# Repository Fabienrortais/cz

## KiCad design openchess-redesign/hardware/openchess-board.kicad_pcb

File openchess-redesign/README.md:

# OpenChess PCB redesign

A complete, single-PCB redesign of the OpenChess smart chess board
(https://joojoooo.github.io/OpenChess/) that keeps **100 % firmware
compatibility** with upstream (including the pre-built binaries), while
replacing the hand-wired "plastic PCB" + perfboard with one assembled board.

## What is on the board

- 8 x 8 squares, **40 mm pitch** (parametric), board 340 x 374 mm, 2 layers.
- Per square: one SOT-23 Hall switch at the square centre (under a 12 mm iron
  disc, silkscreen circle marks it), one WS2812B 5050 LED 9 mm below the
  centre, one 100 nF decoupling cap.
- Column drive: 74HCT595 -> 8 x 1k -> 8 x S8550 PNP high-side switches, one
  under each file, feeding switched +5V up a dedicated trace (same scheme as
  upstream, `SR_INVERT_OUTPUTS = PNP`).
- Rows: sensor open-collector outputs wired-OR per rank, 10k pull-up to 3.3 V,
  straight to the ESP32 GPIOs used by the upstream defaults.
- Controller strip (bottom 42 mm): ESP32-WROOM-32E, CH340C USB-UART with the
  DevKitC auto-reset circuit, RESET/BOOT buttons, AMS1117-3.3, USB-C
  (5 V/3 A, 5.1k CC pull-downs, 3 A polyfuse), optional JST-XH 5 V/4 A input,
  2 x 470 uF bulk, 74AHCT1G125 level shifter for the LED data.
- Power distribution: a 4 mm +5V bus along the strip (B.Cu) and a 2 mm vertical
  +5V bus per file; GND pours on both layers stitched with vias at every square
  corner.
- GPIO map = upstream defaults, so the firmware needs no changes:
  LED IO32, SR SER IO33, SRCLK IO14, RCLK IO26, rows IO4,16,17,18,19,21,22,23.

## Optional battery (both variants)

An IP5306 power-bank IC (Injoinic, LCSC C181692) charges a single Li-ion /
LiPo cell from the USB-C input (2.1 A) and boosts it to 5 V (2.4 A max) for
the board. It is selected with the 3-pin jumper **JP1**:

| JP1 | Bus fed from | Use |
|---|---|---|
| 1-2 | fuse output (USB-C or J2 directly) | no battery fitted; U6/L1/C77-C79/J5/SW3 can be left unpopulated |
| 2-3 | IP5306 VOUT (battery boost, pass-through while charging) | battery fitted on J5 (JST-PH 2.0 mm, + on pin 1) |

Without a battery: use the `-nobattery` BOM/CPL files (block unpopulated),
jumper JP1 1-2, and power through USB-C or J2 as on a board without the block.
SW3 is the IP5306 key (short press on, long press off, it also turns off by
itself below about 45 mA, which the ESP32 never reaches). Power budget: the
boost delivers 2.4 A, so with the battery keep the LED brightness moderate
(all 64 LEDs full white need 3.8 A); a 3000 mAh cell runs the board for
roughly 6-8 h of normal play. Set `OPENCHESS_BATTERY=0` before building to
remove the block entirely.

## Two variants

| Variant | Controller | Output folders | Use when |
|---|---|---|---|
| `module` (default) | ESP32-WROOM-32E soldered on the board, CH340C USB-UART, AMS1117-3.3, RESET/BOOT buttons | `hardware/`, `manufacturing/`, `docs/img/` | You want one fully assembled board from JLCPCB/PCBWay. |
| `nodemcu` | Two 19-pin sockets for a plug-in 38-pin ESP32 dev board (NodeMCU-32S, ESP32-DevKitC V4, ...). USB-C is power only; flashing is done through the dev board's own USB. | `hardware-nodemcu/`, `manufacturing-nodemcu/`, `docs/img-nodemcu/` | You already have a NodeMCU / DevKitC. Strip is 56 mm tall (board 340 x 388 mm). |

NodeMCU variant notes:

- The dev board plugs in with its **antenna to the left and USB to the right**
  (silkscreen says so). Bottom-left pin is 3V3, bottom-right pin is 5V; the
  top row carries GND, IO23, IO22, TX, RX, IO21, GND, IO19, IO18, IO5, IO17,
  IO16, IO4, ... which is the pin order of both the NodeMCU-32S and the
  Espressif DevKitC V4. Check the silkscreen of your board: 3V3 and 5V must
  land on those two corner pins. If a signal pin differs, that is harmless:
  every signal GPIO is configurable in the OpenChess WebUI.
- `DEV_ROW_SPACING` in `design.py` is the distance between the two pin rows:
  22.86 mm (0.9") for the NodeMCU-32S, 25.4 mm (1.0") for the DevKitC V4.
  Measure yours centre-to-centre before ordering.
- No copper pour is placed under the antenna end of the dev board.
- Power the board from the USB-C or J2 (5 V/4 A). Powering only through the
  dev board's micro-USB works for testing but its diode limits LED current.

Build one variant with `VARIANTS=nodemcu ./build.sh /path/to/freerouting.jar`
or set `OPENCHESS_VARIANT=nodemcu` when running the tools by hand.

Folder layout:

```
openchess-redesign/
  AUDIT.md           audit of the upstream project
  README.md          this file
  ORDERING.md        how to order at JLCPCB / PCBWay, cost notes, assembly notes
  hardware/          KiCad project of the module variant (+ DRC report); hardware-nodemcu/ for the dev-board variant
  manufacturing/     gerber zip, drill, JLCPCB BOM + CPL, BOM.md, PDFs (manufacturing-nodemcu/ likewise)
  tools/             generators (everything above is produced from design.py)
  docs/img/          previews
  build.sh           regenerate everything
```

## Regenerating / changing the design

Everything is generated from `tools/design.py` (parts, nets, placement) by
Python scripts that drive KiCad's `pcbnew` module and `kicad-cli`.

KiCad versions: the files were produced with KiCad 7.0.11 (the version
installable in the build container) and use the KiCad 7 file format, which
KiCad 8, 9 and 10 open directly and migrate on save. The scripts detect the
installed version (library paths, API differences, `kicad-cli pcb drc` on 8+)
so you can rebuild with your current KiCad 10 install; the first save from
KiCad 10 will convert the project to the KiCad 10 format.
The matrix routing is scripted; only the controller strip is auto-routed with
Freerouting.

```sh
sudo apt install kicad kicad-symbols kicad-footprints xvfb default-jre   # or any KiCad 8/9/10 install
# Freerouting 1.9.0 jar from https://github.com/freerouting/freerouting/releases
./build.sh /path/to/freerouting.jar
```

Things you will most likely want to change, all at the top of `design.py`:

| Parameter | Default | Note |
|---|---|---|
| `PITCH` | 40.0 mm | Square pitch. 33.33 matches the upstream LED-strip pitch; 45-50 mm for club-size pieces. Board size follows. |
| `SENSOR` | HX3144ESO, pins VCC=1 OUT=2 GND=3 | **Check the datasheet of the exact part you order**; SOT-23 "44E" parts differ between vendors. Any continuous-time open-collector Hall switch in SOT-23 works. |
| `GPIO` | upstream defaults | Only change if you also change the firmware pin config. |
| `STRIP_H`, `MARGIN` | 42 / 10 mm | Controller strip height, grid margin. |

The build verifies the schematic netlist against the model
(`tools/verify_netlist.py`), runs DRC (`tools/drc.py`) and writes
`hardware/openchess-board_drc.rpt`. Opening the project in KiCad and running
"Update PCB from schematic" should report nothing to change.

## Firmware setup on this board

1. Flash the upstream firmware (web flasher or PlatformIO) over the USB-C port
   (CH340C, hold BOOT if needed; the auto-reset circuit normally handles it).
2. In the WebUI "GPIO" section keep the defaults and set the shift-register
   output type to **PNP**.
3. Run the calibration (serial monitor, 115200 baud) once: it learns the LED
   order and the row/column mapping.

## Printable enclosure

`enclosure/enclosure.scad` (OpenSCAD) builds a tray, a 4-piece top plate and a
2-piece controller-strip cover from the same parameters as the PCB
(`tools/gen_enclosure.py` writes `enc_params.scad` and renders the STLs into
`enclosure/stl/` for the module variant and `enclosure/stl-nodemcu/` for the
NodeMCU variant). Every piece is under 175 x 195 mm, so all fit a 256 mm bed
(Bambu A1 or similar):

| Part | Pieces | Print orientation / notes |
|---|---|---|
| `top_q00`, `top_q10`, `top_q01`, `top_q11` | 4 quadrants of the playing surface, 4 mm thick | Print playing face DOWN on the bed: the 12.4 mm iron-disc pockets and 9 mm LED pockets then open upwards and need no supports; 0.8 mm skin stays above each LED. Light/white filament lets the LEDs shine through. Grooves mark the squares, coordinates are engraved in the margins. |
| `tray_00` .. `tray_11` | 4 pieces of the base tray | Flat, no supports. M3 screws go up through the countersunk floor holes into the top plate. |
| `cover_0`, `cover_1` | 2 halves of the strip cover | Print top down. Openings for USB-C (in the tray wall), J2 cable, buttons/LED (module) or the dev board's USB (NodeMCU). |

Glue the quadrant joints (they fall on square edges) or add tape underneath.
Iron discs are glued into the pockets from below; magnets go in the pieces
with the S pole down, as upstream.

## Mechanical notes

- Top plate: anything 3-6 mm thick with a 12.2 mm x 1.2 mm pocket for the iron
  disc centred on each square and a window/diffuser over the LED (9 mm below
  centre). Four 160 x 160 mm printed quadrants fit a 256 mm printer bed.
- The ESP32 antenna overhangs the bottom edge by 6 mm with a copper keep-out
  around it; leave that area of the enclosure free of metal.
- Mounting holes: 7 x M3.

## DRC status

Both variants pass KiCad DRC with 0 errors and 0 unconnected items
(`hardware*/openchess-board*_drc.rpt`). The remaining entries in the reports
are warnings: "library footprint" notices (the headless build has no
fp-lib-table), silkscreen overlaps of reference designators, and a few
"track dangling" notes where the autorouter joined a pre-routed stub mid-way.

Build pipeline per variant: `gen_sch.py` -> `verify_netlist.py` -> `gen_pcb.py`
(scripted matrix routing + pre-routed power/USB/ground stubs) -> `route.py`
(Freerouting for the strip, own `.ses` importer) -> `gnd_repair.py` (adds vias
for ground pour islands, bridges split ground clusters) -> `drc.py` ->
`export.py`. `reroute_nets.py NET...` locks everything else and lets the
router redo single nets.

## Known limitations / to verify

- LCSC numbers were filled from memory and are flagged; verify each one in
  the JLCPCB parts library before ordering (see `ORDERING.md`).
- Rotations in the CPL follow KiCad's convention; check the JLCPCB placement
  preview and rotate SOT-23 / SOIC parts if their preview shows pin 1 wrong.
- 2-layer power distribution is sized for about 4 A total LED current; keep
  the firmware brightness sensible or feed 5 V through J2.

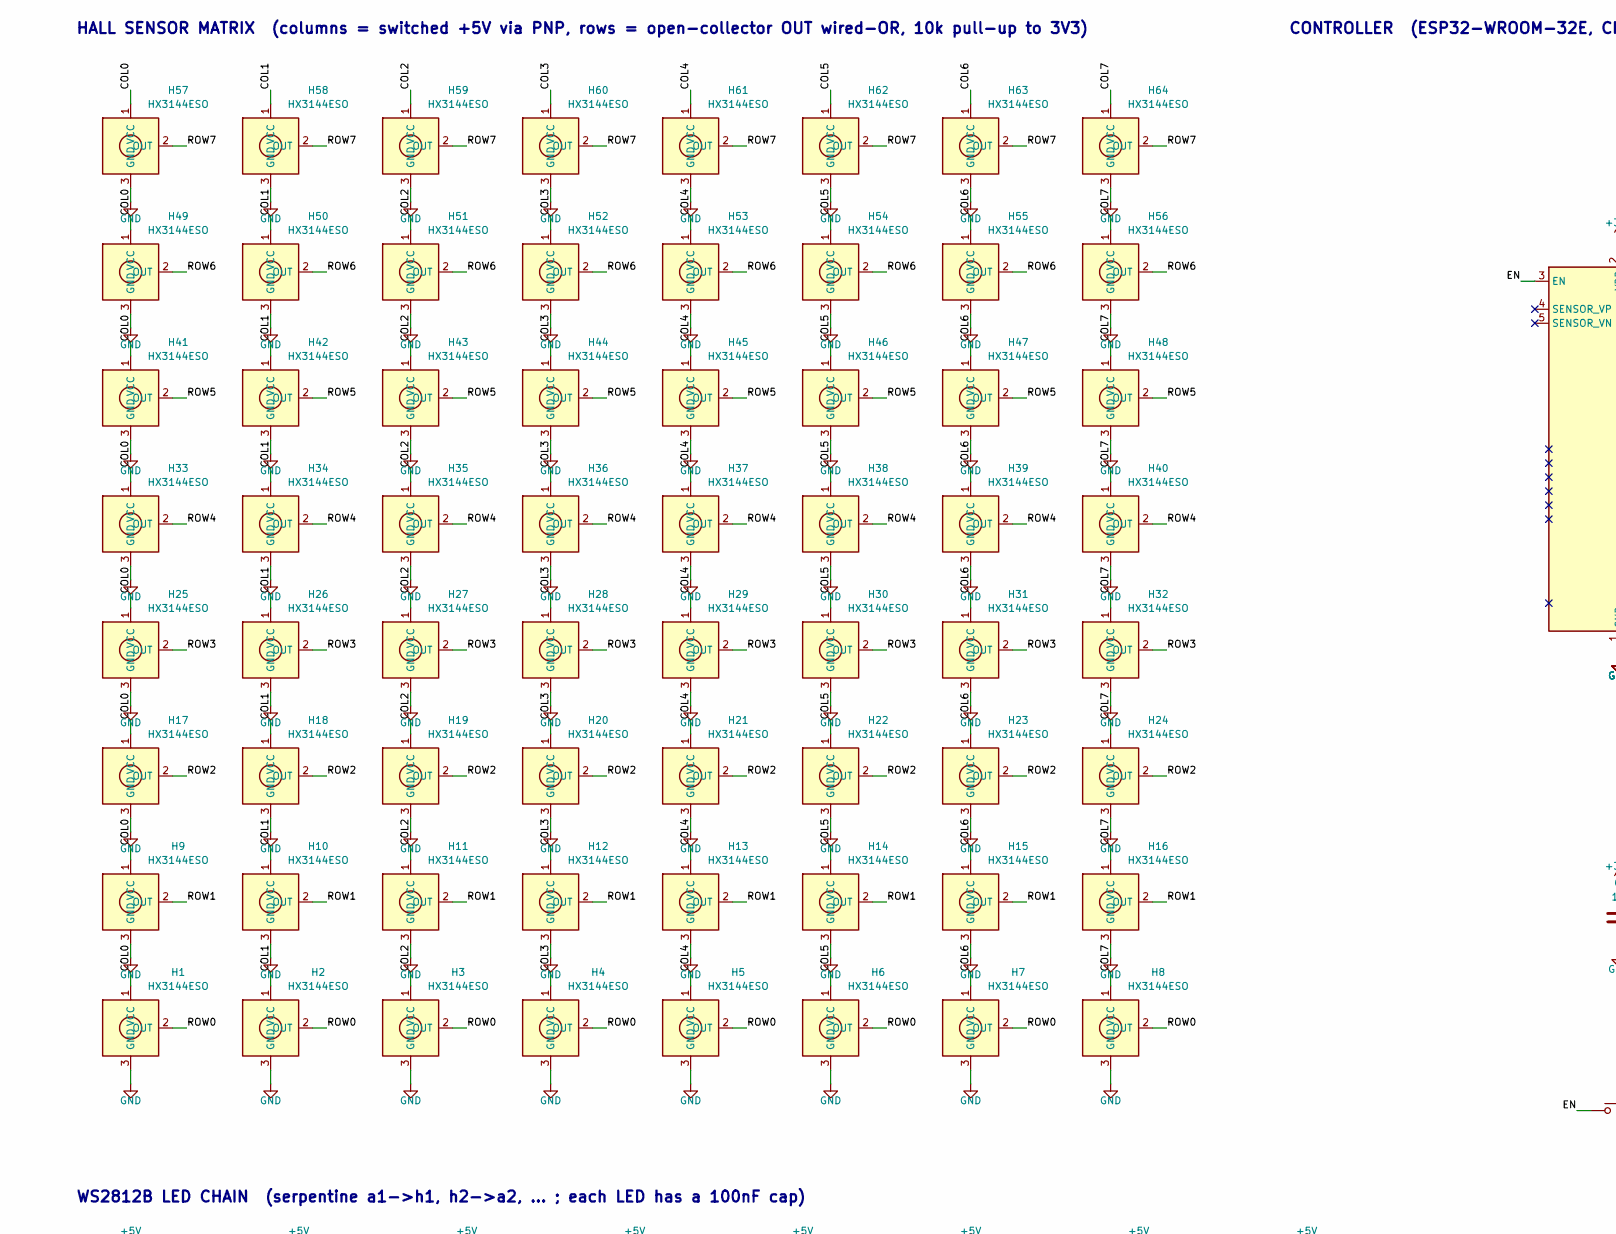
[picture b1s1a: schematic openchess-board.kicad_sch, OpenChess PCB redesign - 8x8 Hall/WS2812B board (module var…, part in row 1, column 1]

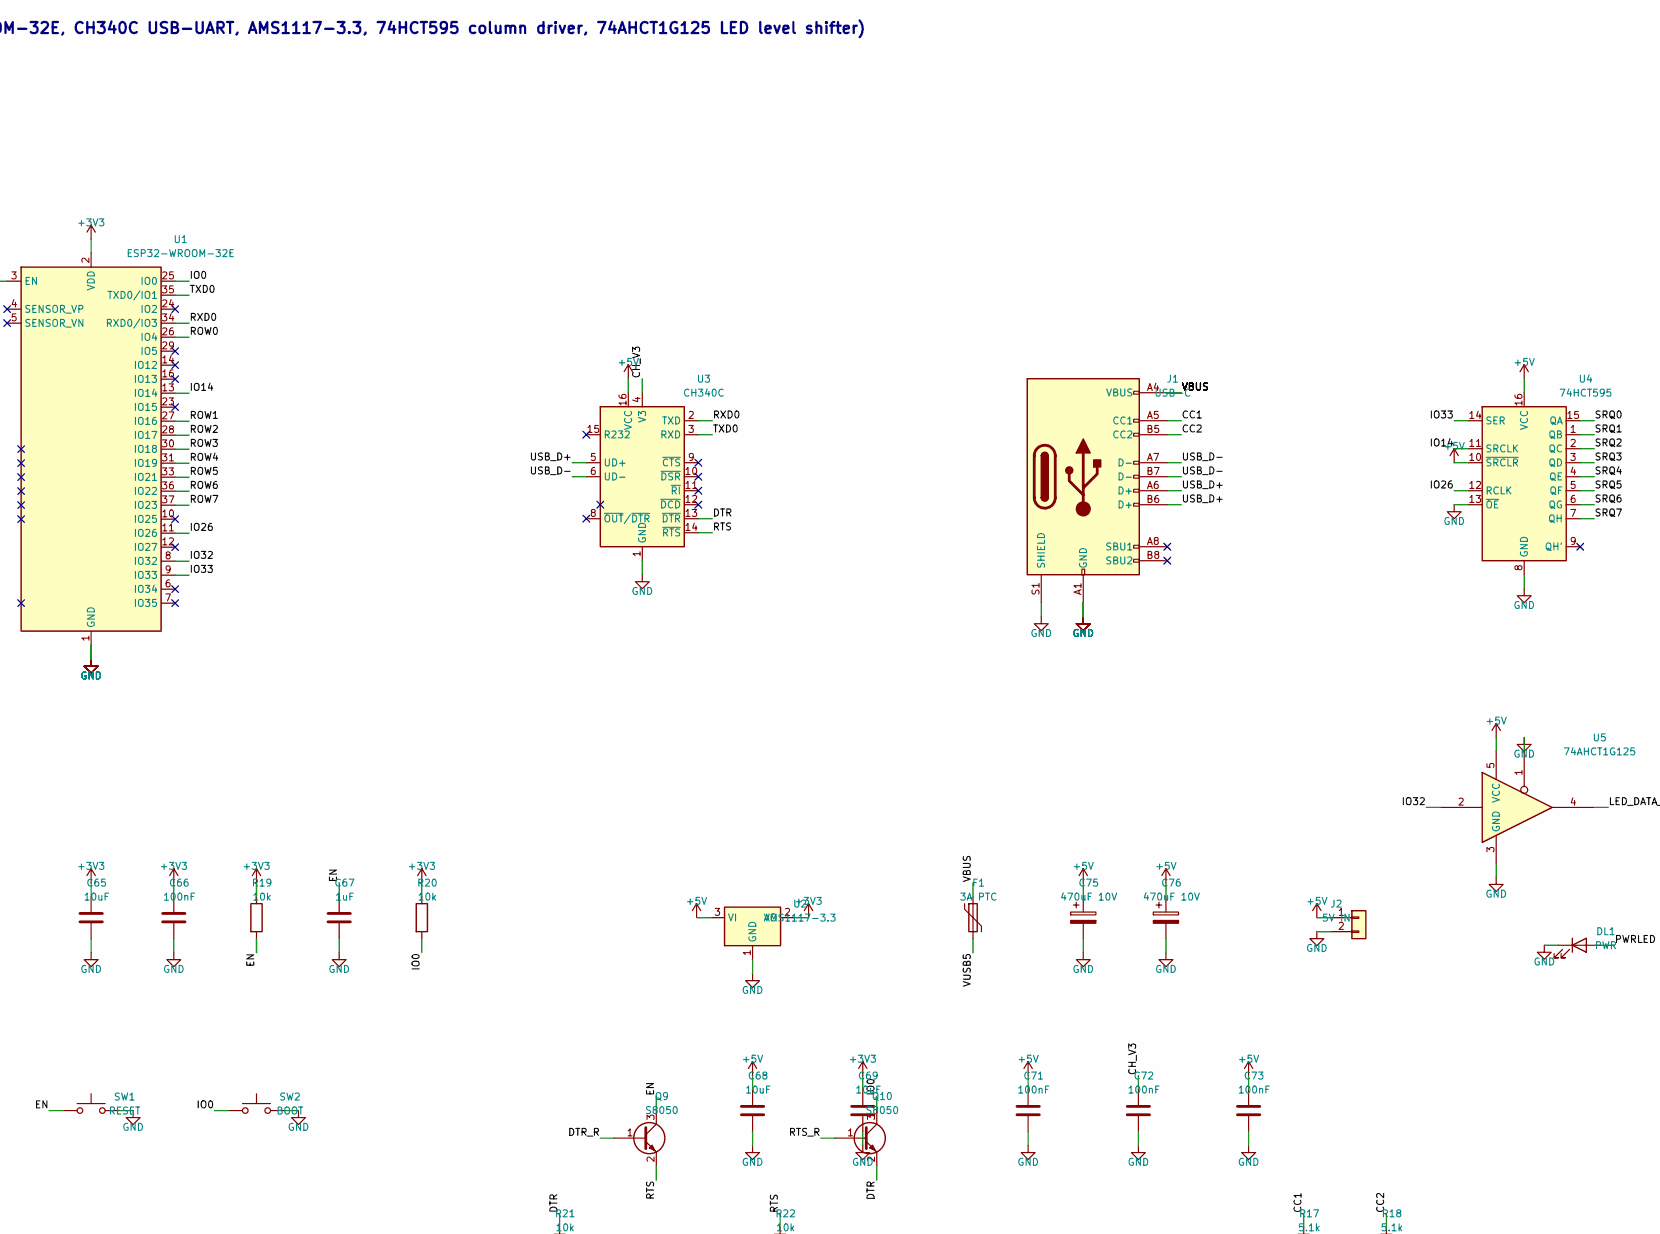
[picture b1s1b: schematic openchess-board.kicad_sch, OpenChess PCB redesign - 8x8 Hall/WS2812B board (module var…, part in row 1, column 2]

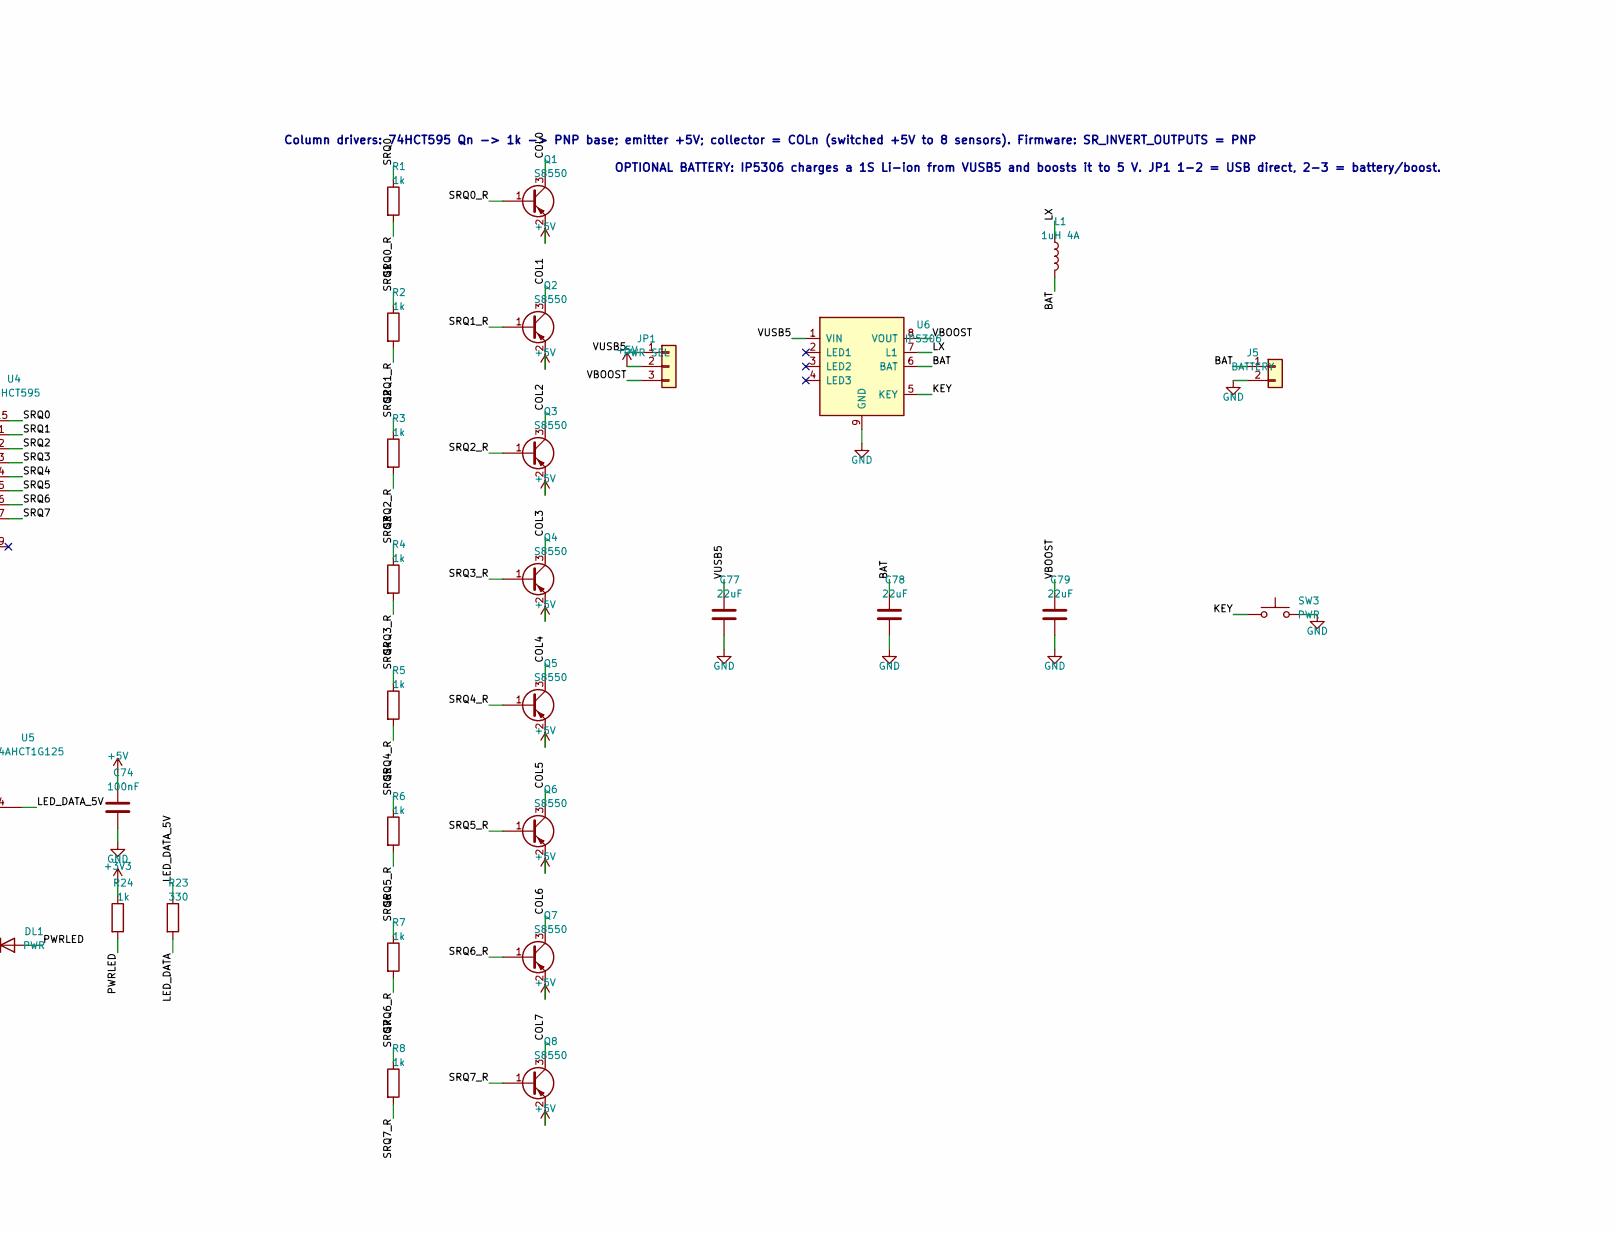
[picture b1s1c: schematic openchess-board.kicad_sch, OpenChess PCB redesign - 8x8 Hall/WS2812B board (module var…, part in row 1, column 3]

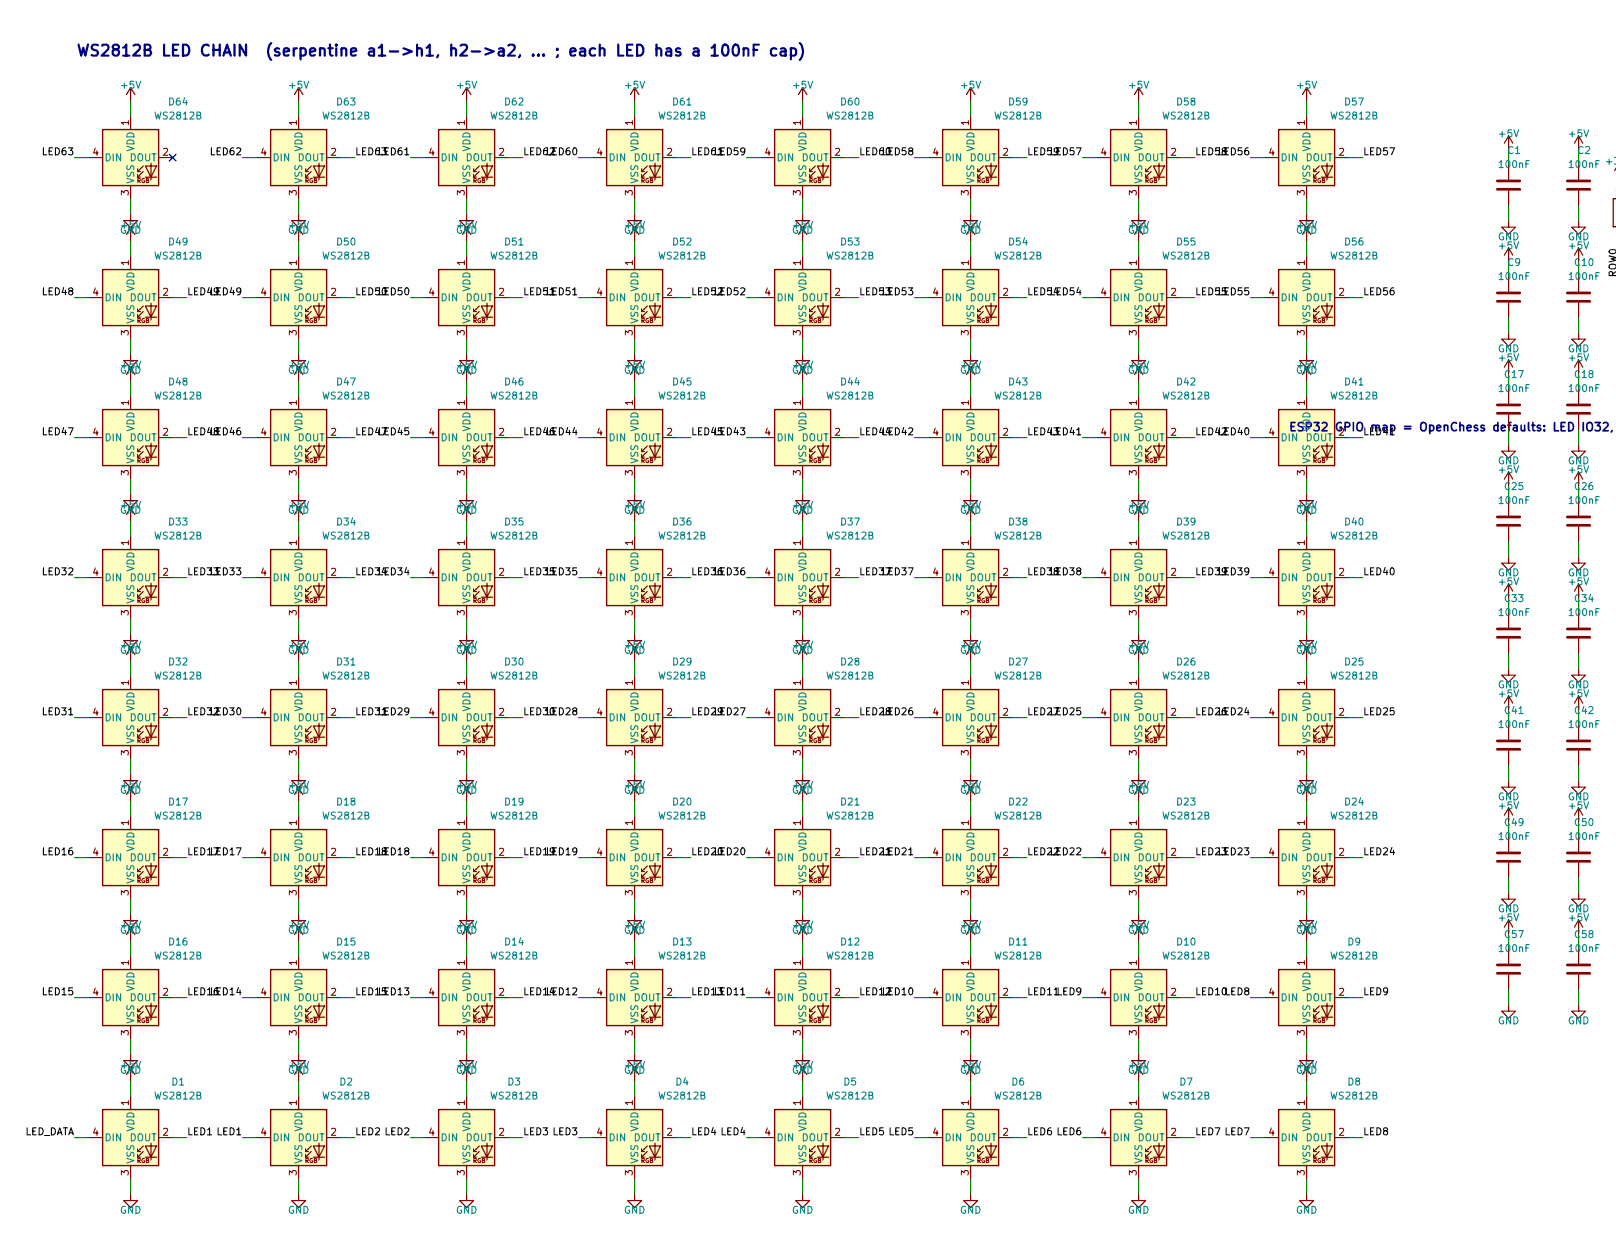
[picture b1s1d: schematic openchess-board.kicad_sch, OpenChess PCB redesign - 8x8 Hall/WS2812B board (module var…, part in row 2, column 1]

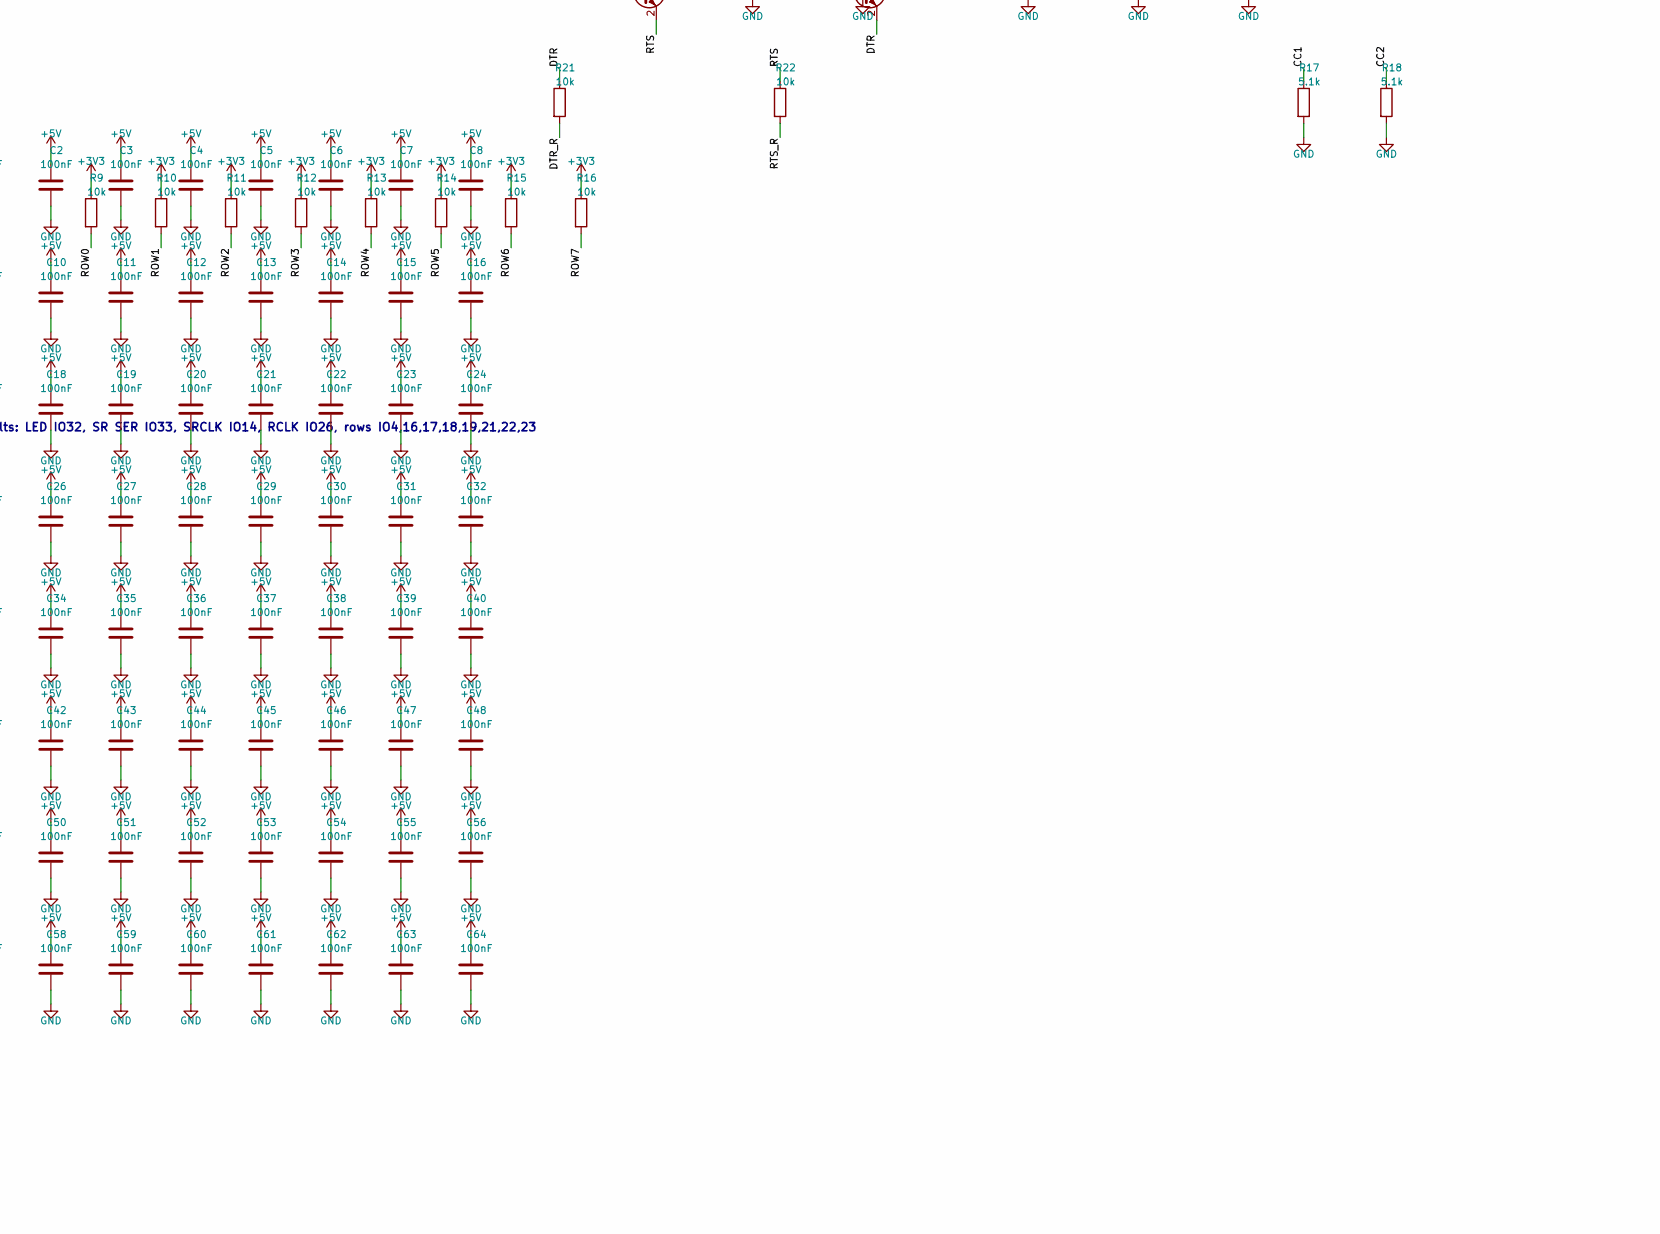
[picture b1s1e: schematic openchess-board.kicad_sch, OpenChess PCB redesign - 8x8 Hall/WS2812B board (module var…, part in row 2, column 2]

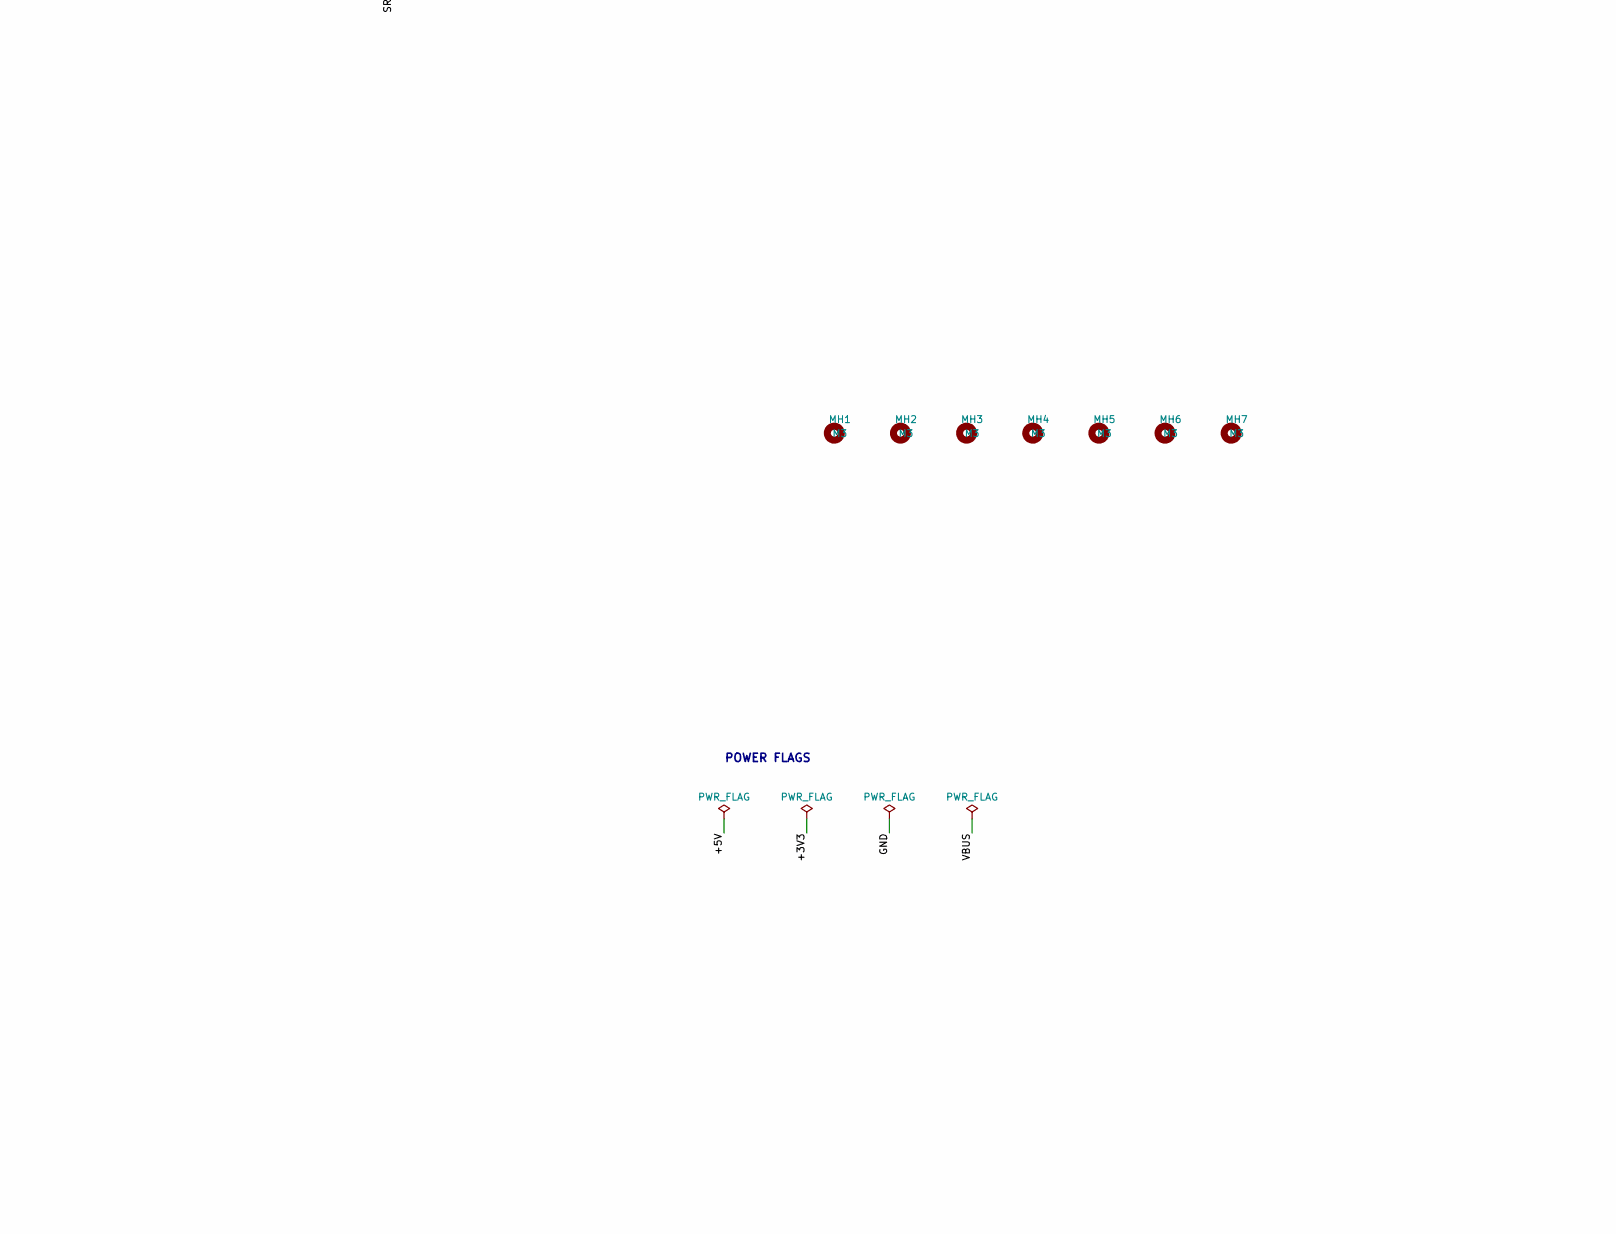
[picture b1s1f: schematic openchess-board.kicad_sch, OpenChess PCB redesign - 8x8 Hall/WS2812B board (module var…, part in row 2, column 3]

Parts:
C1, C2, C3, C4, C5, C6, C7, C8, C9, C10, C11, C12, C13, C14, C15, C16, C17, C18, C19, C20, C21, C22, C23, C24, C25, C26, C27, C28, C29, C30, C31, C32, C33, C34, C35, C36, C37, C38, C39, C40, C41, C42, C43, C44, C45, C46, C47, C48, C49, C50, C51, C52, C53, C54, C55, C56, C57, C58, C59, C60, C61, C62, C63, C64: 100nF; C_0603_1608Metric; MPN CL10B104KB8NNNC; LCSC C14663
C65, C68, C69: 10uF; C_0805_2012Metric; LCSC C15850
C66, C71, C72, C73, C74: 100nF; C_0603_1608Metric; LCSC C14663
C67: 1uF; C_0603_1608Metric; LCSC C15849
C75, C76: 470uF 10V; CP_Elec_8x10; MPN 470uF/10V SMD 8x10
C77, C78, C79: 22uF; C_0805_2012Metric; LCSC C45783
D1, D2, D3, D4, D5, D6, D7, D8, D9, D10, D11, D12, D13, D14, D15, D16, D17, D18, D19, D20, D21, D22, D23, D24, D25, D26, D27, D28, D29, D30, D31, D32, D33, D34, D35, D36, D37, D38, D39, D40, D41, D42, D43, D44, D45, D46, D47, D48, D49, D50, D51, D52, D53, D54, D55, D56, D57, D58, D59, D60, D61, D62, D63, D64: WS2812B; LED_WS2812B_PLCC4_5.0x5.0mm_P3.2mm; MPN WS2812B-B/T; LCSC C2761795
DL1: PWR; LED_0603_1608Metric; LCSC C72043
F1: 3A PTC; Fuse_1812_4532Metric; MPN MF-MSMF300-2 / BSMD1812-300
H1, H2, H3, H4, H5, H6, H7, H8, H9, H10, H11, H12, H13, H14, H15, H16, H17, H18, H19, H20, H21, H22, H23, H24, H25, H26, H27, H28, H29, H30, H31, H32, H33, H34, H35, H36, H37, H38, H39, H40, H41, H42, H43, H44, H45, H46, H47, H48, H49, H50, H51, H52, H53, H54, H55, H56, H57, H58, H59, H60, H61, H62, H63, H64: HX3144ESO; SOT-23; MPN HX3144ESO
J1: USB-C; USB_C_Receptacle_HRO_TYPE-C-31-M-12; MPN TYPE-C-31-M-12; LCSC C165948
J2: 5V IN; JST_XH_B2B-XH-A_1x02_P2.50mm_Vertical; MPN B2B-XH-A; LCSC C158012
J5: BATTERY; JST_PH_B2B-PH-K_1x02_P2.00mm_Vertical; MPN B2B-PH-K-S; LCSC C131337
JP1: PWR SEL; PinHeader_1x03_P2.54mm_Vertical; MPN 1x3 header + jumper; LCSC C2337
L1: 1uH 4A; L_Taiyo-Yuden_NR-60xx; MPN NR6028T1R0N / CD63 1uH >=4A
MH1, MH2, MH3, MH4, MH5, MH6, MH7: M3; MountingHole_3.2mm_M3
Q1, Q2, Q3, Q4, Q5, Q6, Q7, Q8: S8550; SOT-23; MPN S8550; LCSC C2150
Q9, Q10: S8050; SOT-23; MPN S8050; LCSC C2146
R1, R2, R3, R4, R5, R6, R7, R8, R24: 1k; R_0603_1608Metric; LCSC C21190
R9, R10, R11, R12, R13, R14, R15, R16, R19, R20, R21, R22: 10k; R_0603_1608Metric; LCSC C25804
R17, R18: 5.1k; R_0603_1608Metric; LCSC C23186
R23: 330; R_0603_1608Metric; LCSC C23138
SW1: RESET; SW_SPST_TL3342; MPN TS-1187A-B-A-B; LCSC C318884
SW2: BOOT; SW_SPST_TL3342; MPN TS-1187A-B-A-B; LCSC C318884
SW3: PWR; SW_SPST_TL3342; MPN TS-1187A-B-A-B; LCSC C318884
U1: ESP32-WROOM-32E; ESP32-WROOM-32; MPN ESP32-WROOM-32E-N4; LCSC C701341
U2: AMS1117-3.3; SOT-223-3_TabPin2; MPN AMS1117-3.3; LCSC C6186
U3: CH340C; SOIC-16_3.9x9.9mm_P1.27mm; MPN CH340C; LCSC C84681
U4: 74HCT595; SOIC-16_3.9x9.9mm_P1.27mm; MPN SN74HCT595DR / 74HCT595D
U5: 74AHCT1G125; SOT-23-5; MPN SN74AHCT1G125DBVR
U6: IP5306; HSOP-8-1EP_3.9x4.9mm_P1.27mm_EP2.41x3.1mm_ThermalVias; MPN IP5306; LCSC C181692

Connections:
+3V3: C65.1, C66.1, C69.1, R9.1, R10.1, R11.1, R12.1, R13.1, R14.1, R15.1, R16.1, R19.1, R20.1, R24.1, U1.2 (VDD), U2.2 (VO)
+5V: C1.1, C2.1, C3.1, C4.1, C5.1, C6.1, C7.1, C8.1, C9.1, C10.1, C11.1, C12.1, C13.1, C14.1, C15.1, C16.1, C17.1, C18.1, C19.1, C20.1, C21.1, C22.1, C23.1, C24.1, C25.1, C26.1, C27.1, C28.1, C29.1, C30.1, C31.1, C32.1, C33.1, C34.1, C35.1, C36.1, C37.1, C38.1, C39.1, C40.1, C41.1, C42.1, C43.1, C44.1, C45.1, C46.1, C47.1, C48.1, C49.1, C50.1, C51.1, C52.1, C53.1, C54.1, C55.1, C56.1, C57.1, C58.1, C59.1, C60.1, C61.1, C62.1, C63.1, C64.1, C68.1, C71.1, C73.1, C74.1, C75.1, C76.1, D1.1 (VDD), D2.1 (VDD), D3.1 (VDD), D4.1 (VDD), D5.1 (VDD), D6.1 (VDD), D7.1 (VDD), D8.1 (VDD), D9.1 (VDD), D10.1 (VDD), D11.1 (VDD), D12.1 (VDD), D13.1 (VDD), D14.1 (VDD), D15.1 (VDD), D16.1 (VDD), D17.1 (VDD), D18.1 (VDD), D19.1 (VDD), D20.1 (VDD), D21.1 (VDD), D22.1 (VDD), D23.1 (VDD), D24.1 (VDD), D25.1 (VDD), D26.1 (VDD), D27.1 (VDD), D28.1 (VDD), D29.1 (VDD), D30.1 (VDD), D31.1 (VDD), D32.1 (VDD), D33.1 (VDD), D34.1 (VDD), D35.1 (VDD), D36.1 (VDD), D37.1 (VDD), D38.1 (VDD), D39.1 (VDD), D40.1 (VDD), D41.1 (VDD), D42.1 (VDD), D43.1 (VDD), D44.1 (VDD), D45.1 (VDD), D46.1 (VDD), D47.1 (VDD), D48.1 (VDD), D49.1 (VDD), D50.1 (VDD), D51.1 (VDD), D52.1 (VDD), D53.1 (VDD), D54.1 (VDD), D55.1 (VDD), D56.1 (VDD), D57.1 (VDD), D58.1 (VDD), D59.1 (VDD), D60.1 (VDD), D61.1 (VDD), D62.1 (VDD), D63.1 (VDD), D64.1 (VDD), J2.1, JP1.2, Q1.2 (E), Q2.2 (E), Q3.2 (E), Q4.2 (E), Q5.2 (E), Q6.2 (E), Q7.2 (E), Q8.2 (E), U2.3 (VI), U3.16 (VCC), U4.10 (~SRCLR), U4.16 (VCC), U5.5 (VCC)
BAT: C78.1, J5.1, L1.2, U6.6 (BAT)
CC1: J1.A5 (CC1), R17.1
CC2: J1.B5 (CC2), R18.1
CH_V3: C72.1, U3.4 (V3)
COL0: H1.1 (VCC), H9.1 (VCC), H17.1 (VCC), H25.1 (VCC), H33.1 (VCC), H41.1 (VCC), H49.1 (VCC), H57.1 (VCC), Q1.3 (C)
COL1: H2.1 (VCC), H10.1 (VCC), H18.1 (VCC), H26.1 (VCC), H34.1 (VCC), H42.1 (VCC), H50.1 (VCC), H58.1 (VCC), Q2.3 (C)
COL2: H3.1 (VCC), H11.1 (VCC), H19.1 (VCC), H27.1 (VCC), H35.1 (VCC), H43.1 (VCC), H51.1 (VCC), H59.1 (VCC), Q3.3 (C)
COL3: H4.1 (VCC), H12.1 (VCC), H20.1 (VCC), H28.1 (VCC), H36.1 (VCC), H44.1 (VCC), H52.1 (VCC), H60.1 (VCC), Q4.3 (C)
COL4: H5.1 (VCC), H13.1 (VCC), H21.1 (VCC), H29.1 (VCC), H37.1 (VCC), H45.1 (VCC), H53.1 (VCC), H61.1 (VCC), Q5.3 (C)
COL5: H6.1 (VCC), H14.1 (VCC), H22.1 (VCC), H30.1 (VCC), H38.1 (VCC), H46.1 (VCC), H54.1 (VCC), H62.1 (VCC), Q6.3 (C)
COL6: H7.1 (VCC), H15.1 (VCC), H23.1 (VCC), H31.1 (VCC), H39.1 (VCC), H47.1 (VCC), H55.1 (VCC), H63.1 (VCC), Q7.3 (C)
COL7: H8.1 (VCC), H16.1 (VCC), H24.1 (VCC), H32.1 (VCC), H40.1 (VCC), H48.1 (VCC), H56.1 (VCC), H64.1 (VCC), Q8.3 (C)
DTR: Q10.2 (E), R21.1, U3.13 (~DTR)
DTR_R: Q9.1 (B), R21.2
EN: C67.1, Q9.3 (C), R19.2, SW1.1, U1.3 (EN)
GND: C1.2, C2.2, C3.2, C4.2, C5.2, C6.2, C7.2, C8.2, C9.2, C10.2, C11.2, C12.2, C13.2, C14.2, C15.2, C16.2, C17.2, C18.2, C19.2, C20.2, C21.2, C22.2, C23.2, C24.2, C25.2, C26.2, C27.2, C28.2, C29.2, C30.2, C31.2, C32.2, C33.2, C34.2, C35.2, C36.2, C37.2, C38.2, C39.2, C40.2, C41.2, C42.2, C43.2, C44.2, C45.2, C46.2, C47.2, C48.2, C49.2, C50.2, C51.2, C52.2, C53.2, C54.2, C55.2, C56.2, C57.2, C58.2, C59.2, C60.2, C61.2, C62.2, C63.2, C64.2, C65.2, C66.2, C67.2, C68.2, C69.2, C71.2, C72.2, C73.2, C74.2, C75.2, C76.2, C77.2, C78.2, C79.2, D1.3 (VSS), D2.3 (VSS), D3.3 (VSS), D4.3 (VSS), D5.3 (VSS), D6.3 (VSS), D7.3 (VSS), D8.3 (VSS), D9.3 (VSS), D10.3 (VSS), D11.3 (VSS), D12.3 (VSS), D13.3 (VSS), D14.3 (VSS), D15.3 (VSS), D16.3 (VSS), D17.3 (VSS), D18.3 (VSS), D19.3 (VSS), D20.3 (VSS), D21.3 (VSS), D22.3 (VSS), D23.3 (VSS), D24.3 (VSS), D25.3 (VSS), D26.3 (VSS), D27.3 (VSS), D28.3 (VSS), D29.3 (VSS), D30.3 (VSS), D31.3 (VSS), D32.3 (VSS), D33.3 (VSS), D34.3 (VSS), D35.3 (VSS), D36.3 (VSS), D37.3 (VSS), D38.3 (VSS), D39.3 (VSS), D40.3 (VSS), D41.3 (VSS), D42.3 (VSS), D43.3 (VSS), D44.3 (VSS), D45.3 (VSS), D46.3 (VSS), D47.3 (VSS), D48.3 (VSS), D49.3 (VSS), D50.3 (VSS), D51.3 (VSS), D52.3 (VSS), D53.3 (VSS), D54.3 (VSS), D55.3 (VSS), D56.3 (VSS), D57.3 (VSS), D58.3 (VSS), D59.3 (VSS), D60.3 (VSS), D61.3 (VSS), D62.3 (VSS), D63.3 (VSS), D64.3 (VSS), DL1.1 (K), H1.3 (GND), H2.3 (GND), H3.3 (GND), H4.3 (GND), H5.3 (GND), H6.3 (GND), H7.3 (GND), H8.3 (GND), H9.3 (GND), H10.3 (GND), H11.3 (GND), H12.3 (GND), H13.3 (GND), H14.3 (GND), H15.3 (GND), H16.3 (GND), H17.3 (GND), H18.3 (GND), H19.3 (GND), H20.3 (GND), H21.3 (GND), H22.3 (GND), H23.3 (GND), H24.3 (GND), H25.3 (GND), H26.3 (GND), H27.3 (GND), H28.3 (GND), H29.3 (GND), H30.3 (GND), H31.3 (GND), H32.3 (GND), H33.3 (GND), H34.3 (GND), H35.3 (GND), H36.3 (GND), H37.3 (GND), H38.3 (GND), H39.3 (GND), H40.3 (GND), H41.3 (GND), H42.3 (GND), H43.3 (GND), H44.3 (GND), H45.3 (GND), H46.3 (GND), H47.3 (GND), H48.3 (GND), H49.3 (GND), H50.3 (GND), H51.3 (GND), H52.3 (GND), H53.3 (GND), H54.3 (GND), H55.3 (GND), H56.3 (GND), H57.3 (GND), H58.3 (GND), H59.3 (GND), H60.3 (GND), H61.3 (GND), H62.3 (GND), H63.3 (GND), H64.3 (GND), J1.A1 (GND), J1.A12 (GND), J1.B1 (GND), J1.B12 (GND), J1.S1 (SHIELD), J2.2, J5.2, R17.2, R18.2, SW1.2, SW2.2, SW3.2, U1.1 (GND), U1.15 (GND), U1.38 (GND), U1.39 (GND), U2.1 (GND), U3.1 (GND), U4.8 (GND), U4.13 (~OE), U5.1, U5.3 (GND), U6.9 (GND)
IO0: Q10.3 (C), R20.2, SW2.1, U1.25 (IO0)
IO14: U1.13 (IO14), U4.11 (SRCLK)
IO26: U1.11 (IO26), U4.12 (RCLK)
IO32: U1.8 (IO32), U5.2
IO33: U1.9 (IO33), U4.14 (SER)
KEY: SW3.1, U6.5 (KEY)
LED1: D1.2 (DOUT), D2.4 (DIN)
LED2: D2.2 (DOUT), D3.4 (DIN)
LED3: D3.2 (DOUT), D4.4 (DIN)
LED4: D4.2 (DOUT), D5.4 (DIN)
LED5: D5.2 (DOUT), D6.4 (DIN)
LED6: D6.2 (DOUT), D7.4 (DIN)
LED7: D7.2 (DOUT), D8.4 (DIN)
LED8: D8.2 (DOUT), D9.4 (DIN)
LED9: D9.2 (DOUT), D10.4 (DIN)
LED10: D10.2 (DOUT), D11.4 (DIN)
LED11: D11.2 (DOUT), D12.4 (DIN)
LED12: D12.2 (DOUT), D13.4 (DIN)
LED13: D13.2 (DOUT), D14.4 (DIN)
LED14: D14.2 (DOUT), D15.4 (DIN)
LED15: D15.2 (DOUT), D16.4 (DIN)
LED16: D16.2 (DOUT), D17.4 (DIN)
LED17: D17.2 (DOUT), D18.4 (DIN)
LED18: D18.2 (DOUT), D19.4 (DIN)
LED19: D19.2 (DOUT), D20.4 (DIN)
LED20: D20.2 (DOUT), D21.4 (DIN)
LED21: D21.2 (DOUT), D22.4 (DIN)
LED22: D22.2 (DOUT), D23.4 (DIN)
LED23: D23.2 (DOUT), D24.4 (DIN)
LED24: D24.2 (DOUT), D25.4 (DIN)
LED25: D25.2 (DOUT), D26.4 (DIN)
LED26: D26.2 (DOUT), D27.4 (DIN)
LED27: D27.2 (DOUT), D28.4 (DIN)
LED28: D28.2 (DOUT), D29.4 (DIN)
LED29: D29.2 (DOUT), D30.4 (DIN)
LED30: D30.2 (DOUT), D31.4 (DIN)
LED31: D31.2 (DOUT), D32.4 (DIN)
LED32: D32.2 (DOUT), D33.4 (DIN)
LED33: D33.2 (DOUT), D34.4 (DIN)
LED34: D34.2 (DOUT), D35.4 (DIN)
LED35: D35.2 (DOUT), D36.4 (DIN)
LED36: D36.2 (DOUT), D37.4 (DIN)
LED37: D37.2 (DOUT), D38.4 (DIN)
LED38: D38.2 (DOUT), D39.4 (DIN)
LED39: D39.2 (DOUT), D40.4 (DIN)
LED40: D40.2 (DOUT), D41.4 (DIN)
LED41: D41.2 (DOUT), D42.4 (DIN)
LED42: D42.2 (DOUT), D43.4 (DIN)
LED43: D43.2 (DOUT), D44.4 (DIN)
LED44: D44.2 (DOUT), D45.4 (DIN)
LED45: D45.2 (DOUT), D46.4 (DIN)
LED46: D46.2 (DOUT), D47.4 (DIN)
LED47: D47.2 (DOUT), D48.4 (DIN)
LED48: D48.2 (DOUT), D49.4 (DIN)
LED49: D49.2 (DOUT), D50.4 (DIN)
LED50: D50.2 (DOUT), D51.4 (DIN)
LED51: D51.2 (DOUT), D52.4 (DIN)
LED52: D52.2 (DOUT), D53.4 (DIN)
LED53: D53.2 (DOUT), D54.4 (DIN)
LED54: D54.2 (DOUT), D55.4 (DIN)
LED55: D55.2 (DOUT), D56.4 (DIN)
LED56: D56.2 (DOUT), D57.4 (DIN)
LED57: D57.2 (DOUT), D58.4 (DIN)
LED58: D58.2 (DOUT), D59.4 (DIN)
LED59: D59.2 (DOUT), D60.4 (DIN)
LED60: D60.2 (DOUT), D61.4 (DIN)
LED61: D61.2 (DOUT), D62.4 (DIN)
LED62: D62.2 (DOUT), D63.4 (DIN)
LED63: D63.2 (DOUT), D64.4 (DIN)
LED_DATA: D1.4 (DIN), R23.2
LED_DATA_5V: R23.1, U5.4
LX: L1.1, U6.7 (L1)
PWRLED: DL1.2 (A), R24.2
ROW0: H1.2 (OUT), H2.2 (OUT), H3.2 (OUT), H4.2 (OUT), H5.2 (OUT), H6.2 (OUT), H7.2 (OUT), H8.2 (OUT), R9.2, U1.26 (IO4)
ROW1: H9.2 (OUT), H10.2 (OUT), H11.2 (OUT), H12.2 (OUT), H13.2 (OUT), H14.2 (OUT), H15.2 (OUT), H16.2 (OUT), R10.2, U1.27 (IO16)
ROW2: H17.2 (OUT), H18.2 (OUT), H19.2 (OUT), H20.2 (OUT), H21.2 (OUT), H22.2 (OUT), H23.2 (OUT), H24.2 (OUT), R11.2, U1.28 (IO17)
ROW3: H25.2 (OUT), H26.2 (OUT), H27.2 (OUT), H28.2 (OUT), H29.2 (OUT), H30.2 (OUT), H31.2 (OUT), H32.2 (OUT), R12.2, U1.30 (IO18)
ROW4: H33.2 (OUT), H34.2 (OUT), H35.2 (OUT), H36.2 (OUT), H37.2 (OUT), H38.2 (OUT), H39.2 (OUT), H40.2 (OUT), R13.2, U1.31 (IO19)
ROW5: H41.2 (OUT), H42.2 (OUT), H43.2 (OUT), H44.2 (OUT), H45.2 (OUT), H46.2 (OUT), H47.2 (OUT), H48.2 (OUT), R14.2, U1.33 (IO21)
ROW6: H49.2 (OUT), H50.2 (OUT), H51.2 (OUT), H52.2 (OUT), H53.2 (OUT), H54.2 (OUT), H55.2 (OUT), H56.2 (OUT), R15.2, U1.36 (IO22)
ROW7: H57.2 (OUT), H58.2 (OUT), H59.2 (OUT), H60.2 (OUT), H61.2 (OUT), H62.2 (OUT), H63.2 (OUT), H64.2 (OUT), R16.2, U1.37 (IO23)
RTS: Q9.2 (E), R22.1, U3.14 (~RTS)
RTS_R: Q10.1 (B), R22.2
RXD0: U1.34 (RXD0/IO3), U3.2 (TXD)
SRQ0: R1.1, U4.15 (QA)
SRQ0_R: Q1.1 (B), R1.2
SRQ1: R2.1, U4.1 (QB)
SRQ1_R: Q2.1 (B), R2.2
SRQ2: R3.1, U4.2 (QC)
SRQ2_R: Q3.1 (B), R3.2
SRQ3: R4.1, U4.3 (QD)
SRQ3_R: Q4.1 (B), R4.2
SRQ4: R5.1, U4.4 (QE)
SRQ4_R: Q5.1 (B), R5.2
SRQ5: R6.1, U4.5 (QF)
SRQ5_R: Q6.1 (B), R6.2
SRQ6: R7.1, U4.6 (QG)
SRQ6_R: Q7.1 (B), R7.2
SRQ7: R8.1, U4.7 (QH)
SRQ7_R: Q8.1 (B), R8.2
TXD0: U1.35 (TXD0/IO1), U3.3 (RXD)
USB_D+: J1.A6 (D+), J1.B6 (D+), U3.5 (UD+)
USB_D-: J1.A7 (D-), J1.B7 (D-), U3.6 (UD-)
VBOOST: C79.1, JP1.3, U6.8 (VOUT)
VBUS: F1.1, J1.A4 (VBUS), J1.A9 (VBUS), J1.B4 (VBUS), J1.B9 (VBUS)
VUSB5: C77.1, F1.2, JP1.1, U6.1 (VIN)

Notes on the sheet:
HALL SENSOR MATRIX (columns = switched +5V via PNP, rows = open-collector OUT wired-OR, 10k pull-up to 3V3)
WS2812B LED CHAIN (serpentine a1->h1, h2->a2, ... ; each LED has a 100nF cap)
CONTROLLER (ESP32-WROOM-32E, CH340C USB-UART, AMS1117-3.3, 74HCT595 column driver, 74AHCT1G125 LED level shifter)
OPTIONAL BATTERY: IP5306 charges a 1S Li-ion from VUSB5 and boosts it to 5 V. JP1 1-2 = USB direct, 2-3 = battery/boost.
Column drivers: 74HCT595 Qn -> 1k -> PNP base; emitter +5V; collector = COLn (switched +5V to 8 sensors). Firmware: SR_INVERT_OUTPUTS = PNP
ESP32 GPIO map = OpenChess defaults: LED IO32, SR SER IO33, SRCLK IO14, RCLK IO26, rows IO4,16,17,18,19,21,22,23
POWER FLAGS
